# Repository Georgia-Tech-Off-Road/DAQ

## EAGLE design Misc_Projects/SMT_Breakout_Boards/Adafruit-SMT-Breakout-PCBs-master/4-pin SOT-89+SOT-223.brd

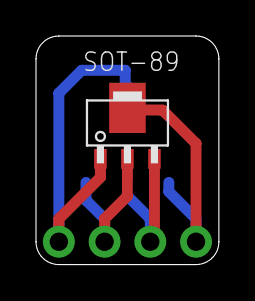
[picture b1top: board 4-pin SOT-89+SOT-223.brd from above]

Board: 2 copper layers, 10.2 x 12.7 mm, 3 parts (1 on the bottom side), 4 nets.

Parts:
JP1: PADS-4
U$1: SOT89
U$2: SOT223

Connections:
unnamed: JP1.1, U$1.P$1, U$2.P$4
unnamed: JP1.2, U$1.P$2, U$2.P$3
unnamed: JP1.3, U$1.P$3, U$2.P$2
unnamed: JP1.4, U$1.P$4, U$2.P$1

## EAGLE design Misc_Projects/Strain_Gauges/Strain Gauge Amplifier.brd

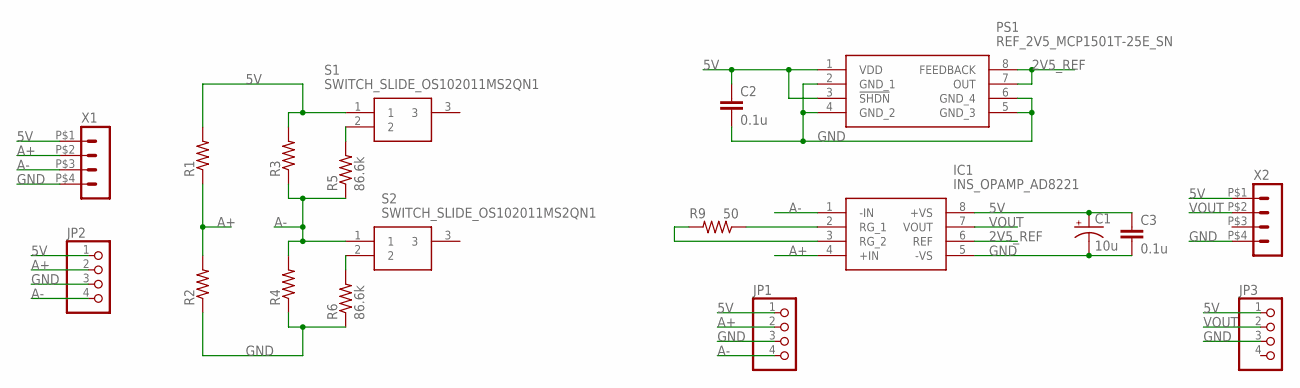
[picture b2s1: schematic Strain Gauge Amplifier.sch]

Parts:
C1: 10u; E2-5
C2, C3: 0.1u; C0603
IC1: INS_OPAMP_AD8221; SOP65P490X110-8N
JP1, JP2, JP3: PINHD-1X4; 1X04
PS1: REF_2V5_MCP1501T-25E_SN; SOIC127P600X175-8N
R1, R2, R3, R4: RES_SMDR1206; R1206
R5, R6: 86.6k; R0603
R9: 50; R0603
S1, S2: SWITCH_SLIDE_OS102011MS2QN1; OS102011MA1QN1
X1, X2: HEADER_POS4_43045-0401; 43045-0400

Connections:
2V5_REF: IC1.6 (REF), PS1.7 (OUT), PS1.8 (FEEDBACK)
5V: C1.+, C2.1, C3.1, IC1.8 (+VS), JP1.1, JP2.1, JP3.1, PS1.1 (VDD), PS1.3 (!SHDN), R1.2, R3.2, S1.1, X1.P$1 (1), X2.P$1 (1)
A+: IC1.4 (+IN), JP1.2, JP2.2, R1.1, R2.2, X1.P$2 (2)
A-: IC1.1 (-IN), JP1.4, JP2.4, R3.1, R4.2, R5.1, S2.1, X1.P$3 (3)
GND: C1.-, C2.2, C3.2, IC1.5 (-VS), JP1.3, JP2.3, JP3.3, PS1.2 (GND_1), PS1.4 (GND_2), PS1.5 (GND_3), PS1.6 (GND_4), R2.1, R4.1, R6.1, X1.P$4 (4), X2.P$4 (4)
unnamed: R6.2, S2.2
unnamed: IC1.2 (RG_1), R9.1
unnamed: IC1.3 (RG_2), R9.2
unnamed: R5.2, S1.2
VOUT: IC1.7 (VOUT), JP3.2, X2.P$2 (2)

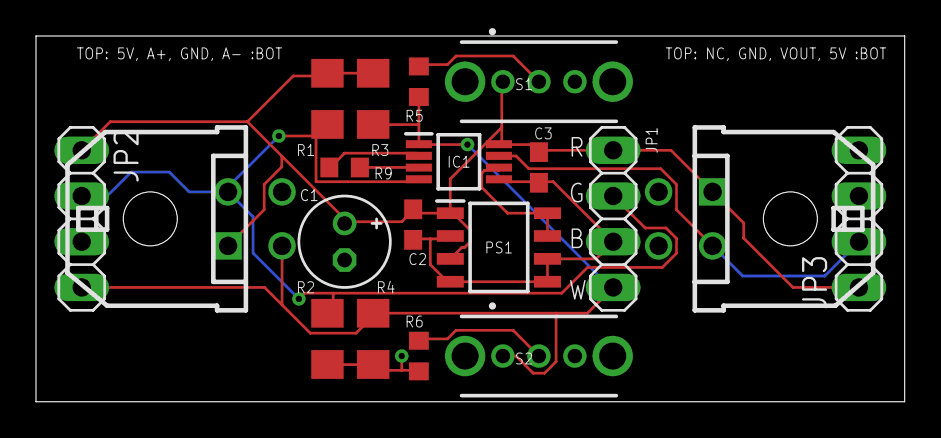
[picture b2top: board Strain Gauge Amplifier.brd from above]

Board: 2 copper layers, 48.3 x 20.3 mm, 19 parts (0 on the bottom side), 10 nets.

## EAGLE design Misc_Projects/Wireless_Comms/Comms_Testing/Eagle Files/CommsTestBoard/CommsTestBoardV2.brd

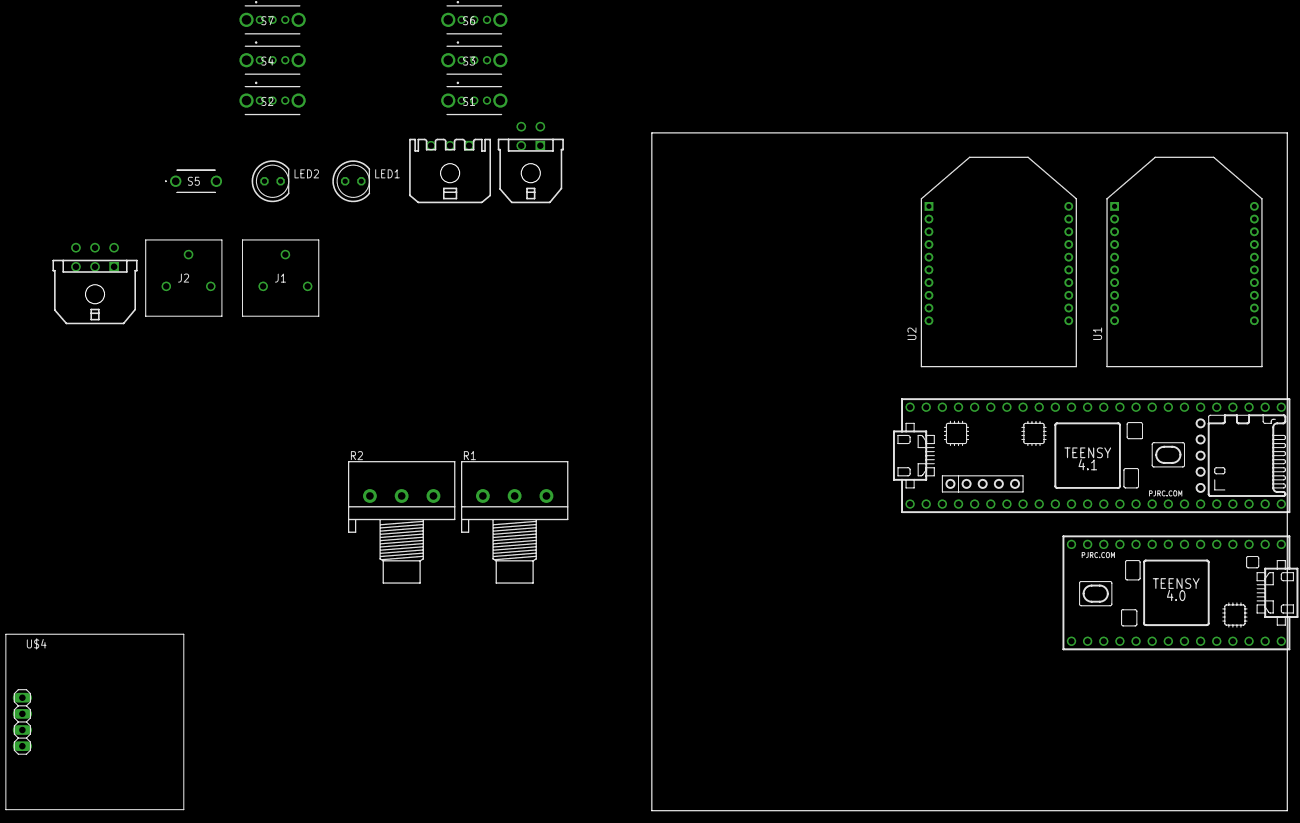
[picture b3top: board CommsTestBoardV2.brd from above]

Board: 2 copper layers, 100.0 x 106.7 mm, 21 parts (0 on the bottom side), 26 nets, no tracks yet.

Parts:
J1, J2: 1985205
LED1, LED2: LED-5MM
R1, R2: 3RP/1610N
S1, S2, S3, S4, S6, S7: SWITCH_SLIDE_OS102011MS2QN1; OS102011MA1QN1
S5: PTS636_SL50_LFS; PTS636SL50LFS
U1, U2: XBEE_PRO_S3B
U$1: TEENSY_4.0_SIMPLE
U$3: TEENSY_4.1_SIMPLE
U$4: OLED_SSD1306
X1: 43045-0400
X2: 43650-0300
X3: 43045-0600

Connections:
3V3: J1.1, J2.1, R1.3, R2.3, U1.1, U$3.3V3_LO, U$4.VCC, X1.P$1, X2.P$1, X3.P$1
5V: U$1.VIN, U$3.VIN
A1: U$3.17/A3, X2.P$2
C1: J1.2, U$1.14/A0
C2: J2.2, U$3.14/A0
CS: U$3.10/CS, X3.P$5
DP: S5.1, U$3.2
GND: J1.3, J2.3, LED1.K, LED2.K, R1.1, R2.1, S5.2, U1.10, U2.1, U2.10, U$1.GND2, U$3.GND2, U$4.GND, X1.P$4, X2.P$3, X3.P$6
LED1: LED1.A, U$1.15/A1
LED2: LED2.A, U$3.15/A1
MISO: U$3.12/MISO, X3.P$3
MOSI: U$3.11/MOSI, X3.P$2
P1: R1.2, U$1.16/A2
P2: R2.2, U$3.16/A2
RX1_4.1: S2.2, U$3.0/RX
RX5_4.0: S7.2, U$1.22/A8
RX_XBEE: S3.2, U1.3
RX_XBEE_SECONDARY: S6.2, U2.3
SCK: U$3.13/SCK, X3.P$4
SCL: U$3.19/A5/SCL, U$4.SCL, X1.P$3
SDA: U$3.18/A4/SDA, U$4.SDA, X1.P$2
TX1_4.1: S1.1, U$3.1/TX
TX2_4.1: S3.1, U$3.8
TX5_4.0: S6.1, U$1.21/A7
TX_XBEE: S4.1, U1.2
TX_XBEE_SECONDARY: S7.1, U2.2

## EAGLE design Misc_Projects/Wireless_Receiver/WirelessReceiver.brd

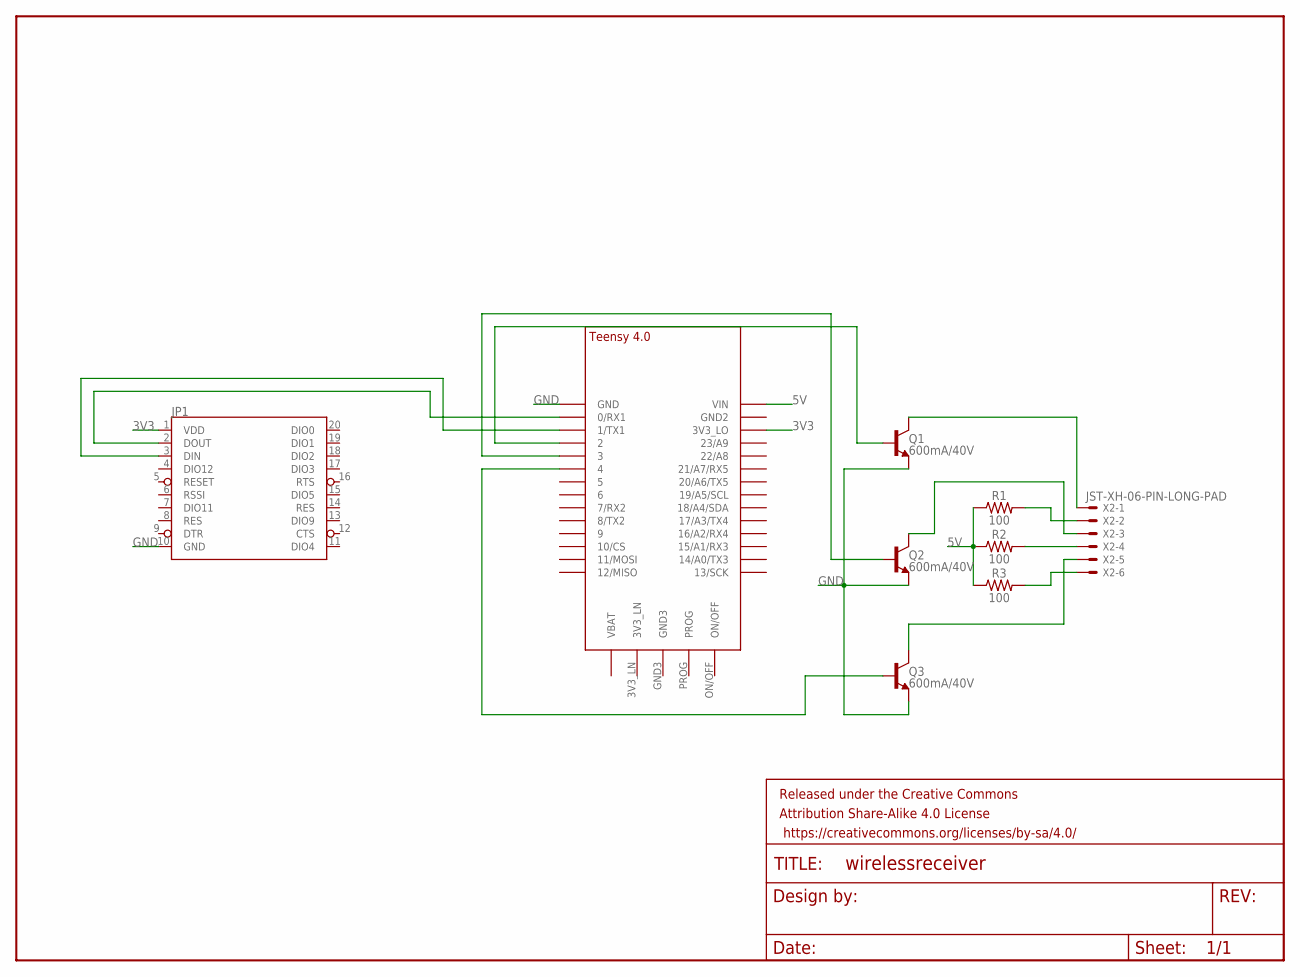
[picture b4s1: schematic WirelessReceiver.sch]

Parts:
FRAME1: FRAME-LETTERNO_PACKAGE; DUMMY
JP1: XBEE
Q1, Q2, Q3: 600mA/40V; SOT23-3
R1, R2, R3: 100; AXIAL-0.3
U$1: TEENSY_4.0-BASIC
X2: JST-XH-06-PIN-LONG-PAD; JST-XH-06-PACKAGE-LONG-PAD

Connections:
3V3: JP1.1 (VDD), U$1.3V3_LO
5V: R1.P$1 (1), R2.P$1 (1), R3.P$1 (1), U$1.VIN
GND: JP1.10 (GND), Q1.2 (E), Q2.2 (E), Q3.2 (E), U$1.GND
unnamed: JP1.2 (DOUT), U$1.0/RX (0/RX1)
unnamed: JP1.3 (DIN), U$1.1/TX (1/TX1)
unnamed: R1.P$2 (2), X2.2
unnamed: R2.P$2 (2), X2.4
unnamed: R3.P$2 (2), X2.6
unnamed: Q1.3 (C), X2.1
unnamed: Q2.3 (C), X2.3
unnamed: Q3.3 (C), X2.5
unnamed: Q1.1 (B), U$1.2
unnamed: Q2.1 (B), U$1.3/CANTX (3)
unnamed: Q3.1 (B), U$1.4/CANRX (4)

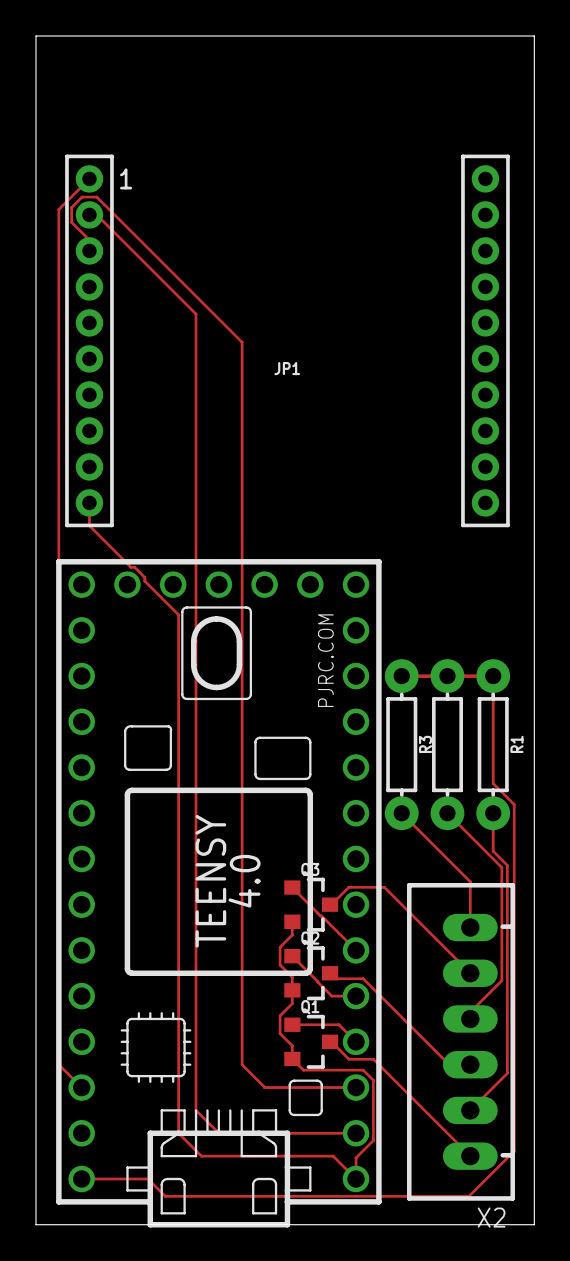
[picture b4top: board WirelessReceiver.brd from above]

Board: 2 copper layers, 27.7 x 66.0 mm, 10 parts (0 on the bottom side), 14 nets.

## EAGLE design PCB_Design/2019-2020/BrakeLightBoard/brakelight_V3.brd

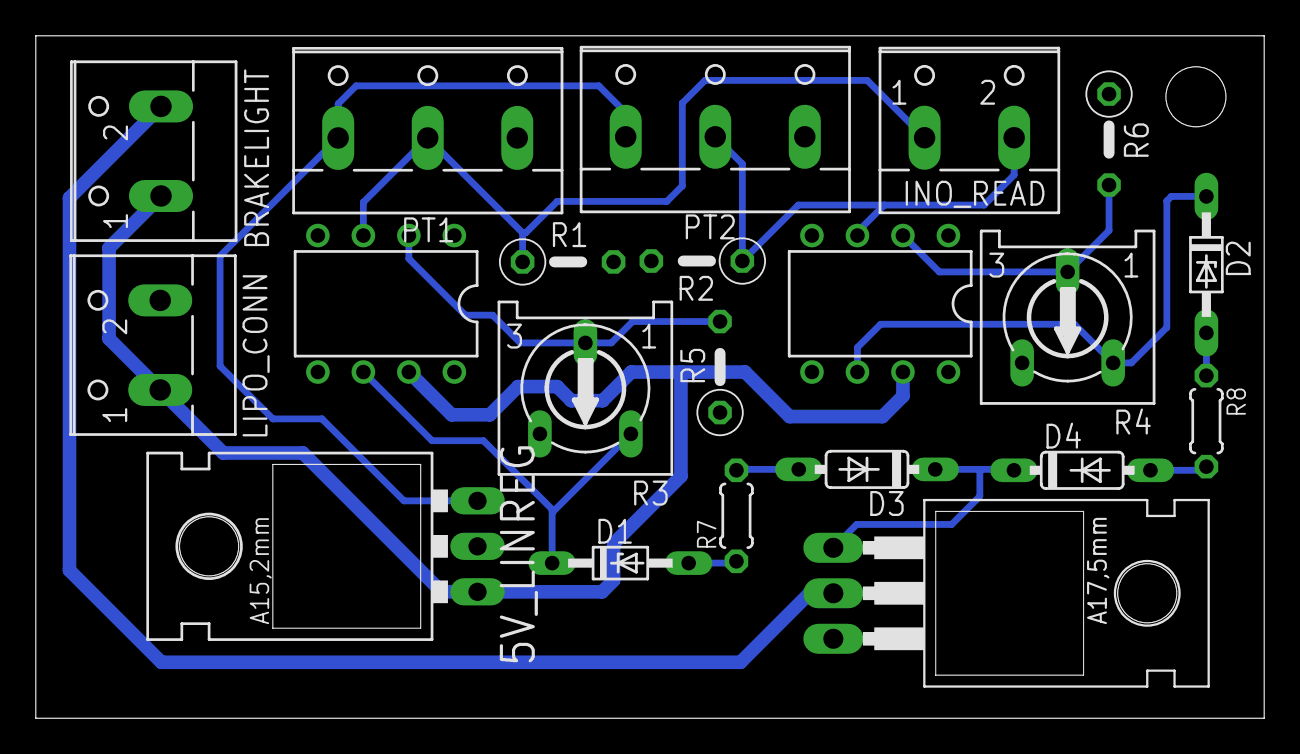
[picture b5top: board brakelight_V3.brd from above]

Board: 2 copper layers, 68.6 x 38.1 mm, 21 parts (0 on the bottom side), 15 nets.

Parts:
5V_LINREG: 78XXL
BRAKELIGHT: W237-102
D1, D2: 1N5231; DO34Z7
D3, D4: 1N4148DO35-7; DO35-7
INO_READ: W237-102
LIPO_CONN: W237-102
PT1, PT2: W237-103
Q2: 30N06L; TO220
R1, R2: 5.1k; 0207/5V
R3, R4: 10k; RS3
R5, R6: 560; 0207/5V
R7, R8: 1k; 0204/5
U$1, U$2: LM741; DIL08

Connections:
5V: 5V_LINREG.OUT, PT1.1, PT2.1
GND: 5V_LINREG.GND, LIPO_CONN.2, PT1.3, PT2.3, Q2.3, R1.2, R2.2, R5.1, R6.1, U$1.1, U$1.4, U$1.5, U$2.1, U$2.4, U$2.5
unnamed: D2.C, R4.A, U$2.6
unnamed: BRAKELIGHT.2, Q2.2
unnamed: D3.A, R7.2
unnamed: D4.A, R8.2
unnamed: D1.A, R7.1
unnamed: D2.A, R8.1
unnamed: D3.C, D4.C, Q2.1
unnamed: D1.C, R3.A, U$1.6
PT1: INO_READ.1, PT1.2, R1.1, U$1.3
PT2: INO_READ.2, PT2.2, R2.1, U$2.3
THRESH1: R3.S, R5.2, U$1.2
THRESH2: R4.S, R6.2, U$2.2
VCC: 5V_LINREG.IN, BRAKELIGHT.1, LIPO_CONN.1, U$1.7, U$2.7

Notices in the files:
parts and their libraries:
SparkFun-Aesthetics: Licensing: Creative Commons ShareAlike 4.0 International - https://creativecommons.org/licenses/by-sa/4.0
SparkFun-Aesthetics: Released under the Creative Commons Attribution Share-Alike 4.0 License
SparkFun-Aesthetics: https://creativecommons.org/licenses/by-sa/4.0
